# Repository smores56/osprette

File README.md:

The Osprette Family
===================

The Osprette is a 34-key unibody keyboard with pinky clusters, my variation on
Brow's [Balbuzard][balbuzard]. All the revisions and variants share the same
layout and the same firmware, so they live in one repo now, a folder per board:

- [Osprette][v1] (`v1`): the original. Pro-micro compatible, direct solder, with
  bluetooth support if you use a suitable controller
- [Osprette V2][v2] (`v2`): second revision, nicer case, optional hotswap
- [Osprette V3][v3] (`v3`): direct solder for people who want their switches to stay put
- [Osprette MX][mx] (`mx`): the original, but for MX switches
- [Osprangle][osprangle] (`osprangle`): hotswap, so you can try all the choc v2 switches
- [Roadkill][roadkill] (`roadkill`): a tiny one using Kailh's PG1316S butterfly switches

Each folder has its own README with ordering details and pictures.

Every board across both families is listed at [smores56/keyboards][index].

# Firmware

They all share a matrix, so they all run the same firmware: `osprette` in QMK
(once [this PR][qmk-pr] lands) and the `osprette` shield in ZMK. Roadkill doesn't
have firmware yet. My personal keymaps live in [qmk_userspace][qmk_userspace] and
[zmk-config][zmk-config].

# Building

Most of these boards use my [smores.pretty][smores-pretty] KiCad library as a
submodule, so clone with `--recurse-submodules`. The two oldest boards (Osprette
and Osprette MX) instead pull in Foostan's `kbd` and Daprice's
`keyswitches.pretty`.

The split half of the family is [the Clog][clog].

[balbuzard]: https://github.com/brow/balbuzard
[v1]: ./v1
[v2]: ./v2
[v3]: ./v3
[mx]: ./mx
[osprangle]: ./osprangle
[roadkill]: ./roadkill
[qmk-pr]: https://github.com/qmk/qmk_firmware/pull/26450
[qmk_userspace]: https://github.com/smores56/qmk_userspace
[zmk-config]: https://github.com/smores56/zmk-config
[smores-pretty]: https://github.com/smores56/smores.pretty
[clog]: https://github.com/smores56/clog
[index]: https://github.com/smores56/keyboards

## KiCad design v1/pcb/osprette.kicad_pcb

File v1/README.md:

The Osprette
============

The Osprette is a 34-key unibody keyboard, my variation on Brow's
[Balbuzard][balbuzard]. It uses any pro-micro compatible daughterboard, with
bluetooth support by way of battery terminals and a power switch.

# Inspiration

I am a big fan of the [Balbuzard][balbuzard], especially the secret choc version that
Brow sent to me. However, there were some things I wanted to change:

- The halves are too close together: not by much, but a little extra space helps a lot
- The thumbs are uncomfortable: normal choc V1 keycaps have ridges on the edges, so the sideways thumbs hurt after prolonged use
- There are too many keys: I've been using 34 keys happily for a while and don't need the other 4 thumb keys
- Not-aggressive pinky stagger: The pinkies on the original are very Corne staggered, which is fine, but I've been spoiled lately by more comfortable, radical stagger
- No support for a power switch: bluetooth is great when you can afford a compatible MCU, and I wanna throw this thing in a bag without worrying about keypresses

All these things together make this board my next step in pursuing the best 34-key
keeb with comfortable pinkies.

# Ordering One

To order one of these from JLC, just upload the `osprette.zip` archive in the
`pcb` directory to the Order Now page at jlcpcb.com, and make sure to set a 1.6mm
thickness.

# Pictures

[balbuzard]: https://github.com/brow/balbuzard

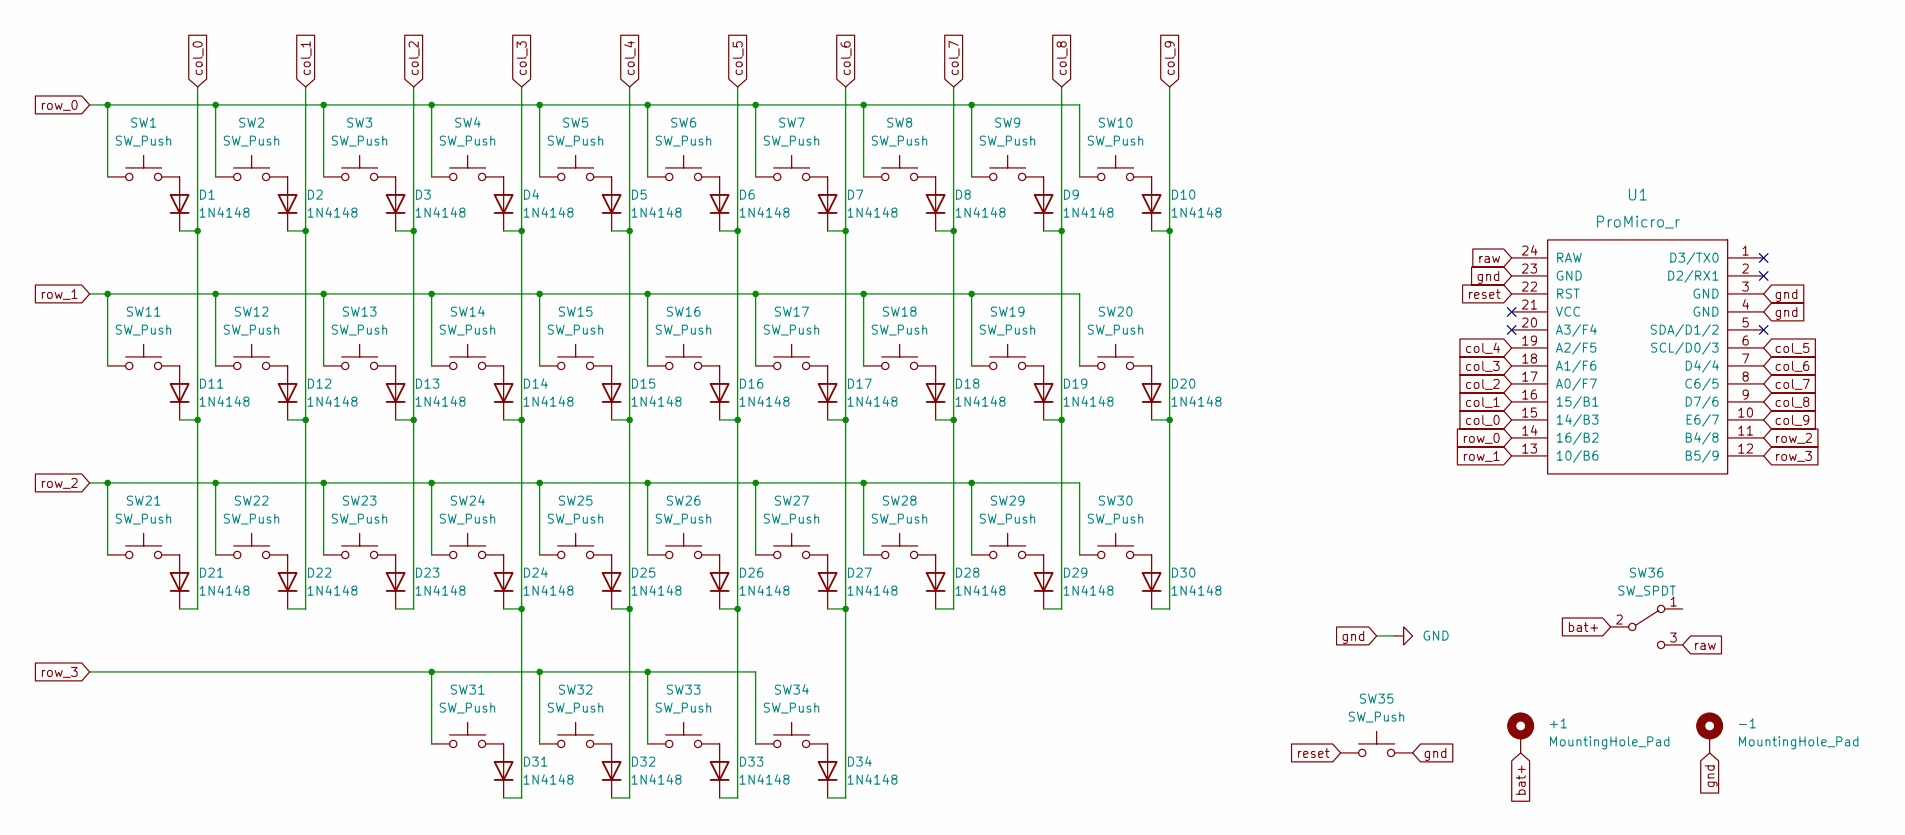
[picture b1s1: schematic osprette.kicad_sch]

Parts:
+1: MountingHole_Pad; 1pin_conn
-1: MountingHole_Pad; 1pin_conn
D1, D2, D3, D4, D5, D6, D7, D8, D9, D10, D11, D12, D13, D14, D15, D16, D17, D18, D19, D20, D21, D22, D23, D24, D25, D26, D27, D28, D29, D30, D31, D32, D33, D34: 1N4148; D_SOD-123
SW1, SW2, SW3, SW4, SW5, SW6, SW7, SW8, SW9, SW10, SW11, SW12, SW13, SW14, SW15, SW16, SW17, SW18, SW19, SW20, SW21, SW22, SW23, SW24, SW25, SW26, SW27, SW28, SW29, SW30, SW31, SW32, SW33, SW34: SW_Push; Kailh_socket_PG1350_optional
SW35: SW_Push; ResetSW
SW36: SW_SPDT; SW_SPDT_PCM12
U1: ProMicro_r; ProMicro_v3.5

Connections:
unnamed: D1.2 (A), SW1.2
unnamed: D2.2 (A), SW2.2
unnamed: D3.2 (A), SW3.2
unnamed: D4.2 (A), SW4.2
unnamed: D5.2 (A), SW5.2
unnamed: D6.2 (A), SW6.2
unnamed: D7.2 (A), SW7.2
unnamed: D8.2 (A), SW8.2
unnamed: D9.2 (A), SW9.2
unnamed: D10.2 (A), SW10.2
unnamed: D11.2 (A), SW11.2
unnamed: D12.2 (A), SW12.2
unnamed: D13.2 (A), SW13.2
unnamed: D14.2 (A), SW14.2
unnamed: D15.2 (A), SW15.2
unnamed: D16.2 (A), SW16.2
unnamed: D17.2 (A), SW17.2
unnamed: D18.2 (A), SW18.2
unnamed: D19.2 (A), SW19.2
unnamed: D20.2 (A), SW20.2
unnamed: D21.2 (A), SW21.2
unnamed: D22.2 (A), SW22.2
unnamed: D23.2 (A), SW23.2
unnamed: D24.2 (A), SW24.2
unnamed: D25.2 (A), SW25.2
unnamed: D26.2 (A), SW26.2
unnamed: D27.2 (A), SW27.2
unnamed: D28.2 (A), SW28.2
unnamed: D29.2 (A), SW29.2
unnamed: D30.2 (A), SW30.2
unnamed: D31.2 (A), SW31.2
unnamed: D32.2 (A), SW32.2
unnamed: D33.2 (A), SW33.2
unnamed: D34.2 (A), SW34.2
bat+: +1.1, SW36.2 (B); also elsewhere on the board
col_0: D1.1 (K), D11.1 (K), D21.1 (K), U1.15 (14/B3)
col_1: D2.1 (K), D12.1 (K), D22.1 (K), U1.16 (15/B1)
col_2: D3.1 (K), D13.1 (K), D23.1 (K), U1.17 (A0/F7)
col_3: D4.1 (K), D14.1 (K), D24.1 (K), D31.1 (K), U1.18 (A1/F6)
col_4: D5.1 (K), D15.1 (K), D25.1 (K), D32.1 (K), U1.19 (A2/F5)
col_5: D6.1 (K), D16.1 (K), D26.1 (K), D33.1 (K), U1.6 (SCL/D0/3)
col_6: D7.1 (K), D17.1 (K), D27.1 (K), D34.1 (K), U1.7 (D4/4)
col_7: D8.1 (K), D18.1 (K), D28.1 (K), U1.8 (C6/5)
col_8: D9.1 (K), D19.1 (K), D29.1 (K), U1.9 (D7/6)
col_9: D10.1 (K), D20.1 (K), D30.1 (K), U1.10 (E6/7)
gnd: -1.1, SW35.2, U1.3 (GND), U1.4 (GND), U1.23 (GND); also elsewhere on the board
raw: SW36.3 (C), U1.24 (RAW)
reset: SW35.1, U1.22 (RST)
row_0: SW1.1, SW2.1, SW3.1, SW4.1, SW5.1, SW6.1, SW7.1, SW8.1, SW9.1, SW10.1, U1.14 (16/B2)
row_1: SW11.1, SW12.1, SW13.1, SW14.1, SW15.1, SW16.1, SW17.1, SW18.1, SW19.1, SW20.1, U1.13 (10/B6)
row_2: SW21.1, SW22.1, SW23.1, SW24.1, SW25.1, SW26.1, SW27.1, SW28.1, SW29.1, SW30.1, U1.11 (B4/8)
row_3: SW31.1, SW32.1, SW33.1, SW34.1, U1.12 (B5/9)

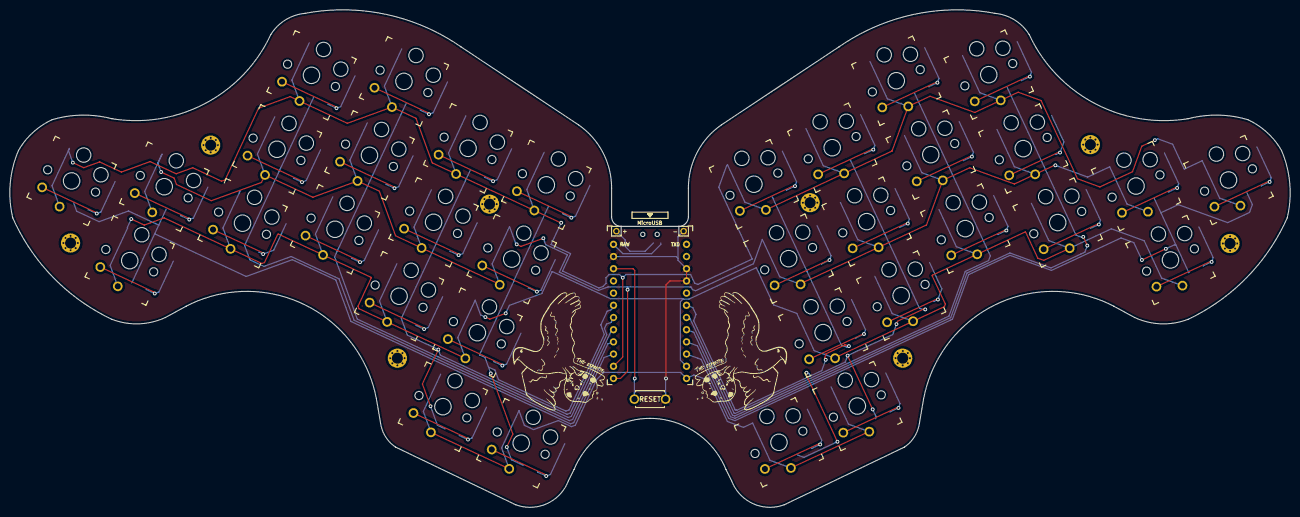
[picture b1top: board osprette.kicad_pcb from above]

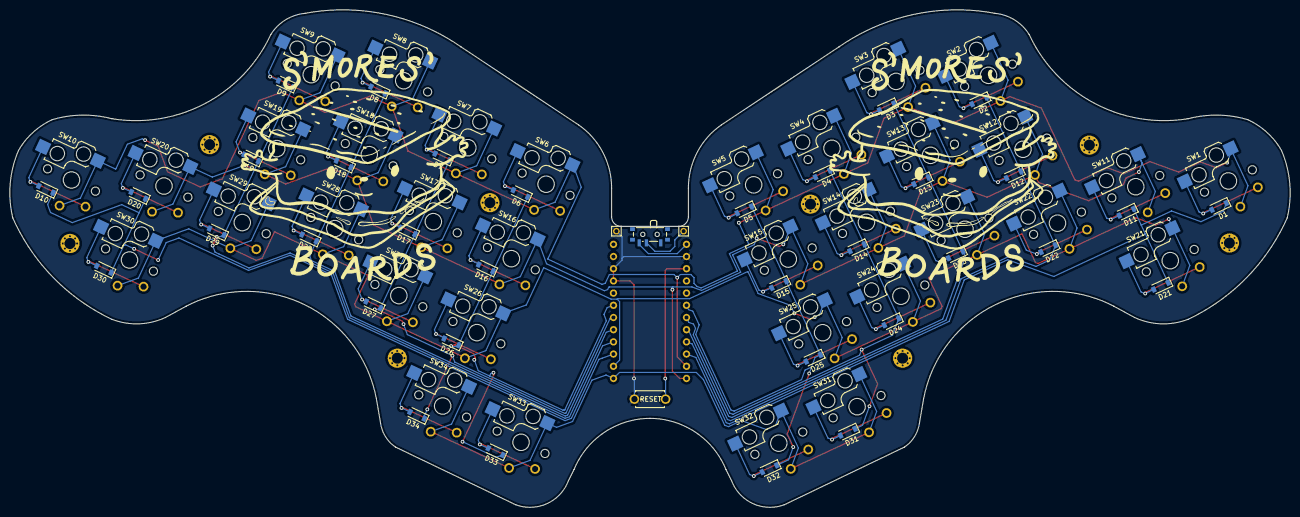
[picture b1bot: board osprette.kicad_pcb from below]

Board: 2 copper layers, 266.8 x 103.7 mm, 81 parts (35 on the bottom side), 52 nets.

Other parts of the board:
+: MountingHole_Pad; 1pin_conn
-: MountingHole_Pad; 1pin_conn
Ref**: Val**; M2_HOLE_v3
Ref**#2, Ref**#3, Ref**#4, Ref**#5, Ref**#6, Ref**#7, Ref**#8: Val**; M2_HOLE_v3

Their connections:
bat+: +.1; also elsewhere on the board
gnd: -.1; also elsewhere on the board

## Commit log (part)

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2021-09-23 finalize design, add silk
2021-09-25 finish case, add readme
2021-09-25 fix typos
2021-09-27 use offset for cleaner case brim, add better battery area
2021-09-27 fix submodules part 1
2021-09-27 fix submodules part 2
2021-09-28 widen usb aperture, strengthen struts
2021-10-08 add images
2021-10-10 Add favicon for BigCartel
2021-10-11 Add MIT License
2021-10-13 Add (many!) GND vias, to expand copper pours
2021-10-14 Add '$fn=100' parameter to circle() SCAD primitives
2021-10-14 update art, remove copper islands, cleanup case
2021-10-24 update art to be rendered correctly
2021-11-05 re-thicken mounting structure
2021-11-05 hide G*** symbol
2023-04-22 Move Pictures to Bottom of README
